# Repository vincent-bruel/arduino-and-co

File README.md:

# arduino-and-co

## Projects involving Arduino, ESP8266, ESP32:
	1. Control a dust collector with magnetic sensors on blast gates

	2. Highlight a photo frame with backlight, led pointing at locations and LCD screen displaying location names

	3. Display weather forecast with an ESP32 and 4x8x8 dot matrix led

	4. Display youtube channel statistics (subscribers) with an ESP32 and 4x8x8 dot matrix led

	5. Get asleep in a few minutes with an arduino Nano and one RGB led like NeoPixel.

   Take a look at my Youtube Channel, there will be Videos for some of these projects.

   I will maintain a list here when they become available:
   
## These projects use my own libraries that are stored in CommonLibraries subdirectory.

## These projects use some third party libraries for which I will maintain a list here.
1. 
2. 
3. 
4. 
5. 
6.

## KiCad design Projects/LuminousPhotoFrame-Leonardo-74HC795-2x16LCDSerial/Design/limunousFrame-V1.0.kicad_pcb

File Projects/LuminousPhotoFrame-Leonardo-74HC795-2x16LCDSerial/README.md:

## Subject: Backlight a photo :camera: (inside a wood or aluminium frame :framed_picture:), 
and place behind some leds and a lcd 16x2 chars
to point/highlight some locations into the photo.

## Example with a polycarbonate front panel

## Schema

## Mandatory Libraries, to install BEFORE programming the sketch to the Arduino:
	Arduino standard SoftwareSerial
	
## Hardware
1. Arduino Leonardo or any Arduino that works with 5V (Nano, Mega, ...)
2. 16 Red led (16 is a maximum)
3. 16 resistor 220ohms 1/4W (16 is a maximum)
4. 2 shift register 74HC795 (each drives 8 leds)
5. Some cable (length depending of your frame's width in centimeters)	
6. A 5V power supply (500mA should be large enough)

## Pinout mapping
See file LuminousFrameFritzing.jpg

## What do you have to tune ?
1. Place leds behind you photo (2cm behind to obtain a sweet spot of approx 1cm on the photo)
2. Change names in the .ino according to the place names or buildings/things you have put a led behind.
3. Put a led strip (NOT controlled by Arduino), around the frame on the back of the photo.

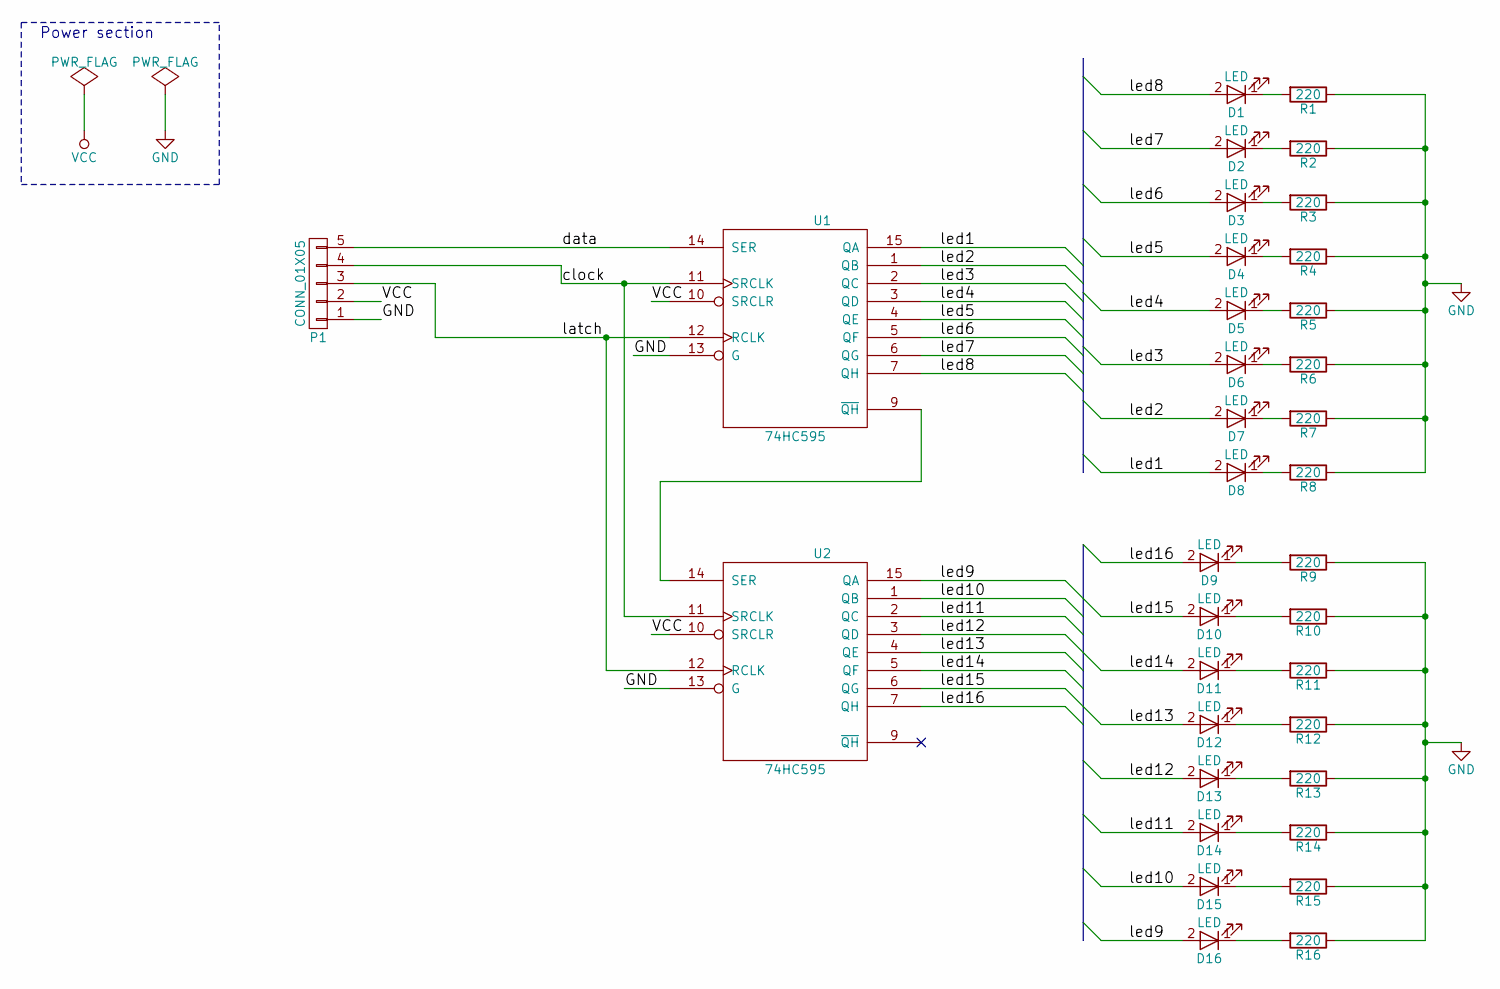
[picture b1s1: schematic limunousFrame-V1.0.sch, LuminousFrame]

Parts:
D1, D2, D3, D4, D5, D6, D7, D8, D9, D10, D11, D12, D13, D14, D15, D16: LED; D_5W_P5.08mm_Vertical_AnodeUp
P1: CONN_01X05; bornier5
R1, R2, R3, R4, R5, R6, R7, R8, R9, R10, R11, R12, R13, R14, R15, R16: 220; R_Axial_Power_L20.0mm_W6.4mm_P5.08mm_Vertical
U1, U2: 74HC595; DIP-16_W7.62mm

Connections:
/clock: P1.4, U1.11 (SRCLK), U2.11 (SRCLK)
/data: P1.5, U1.14 (SER)
/latch: P1.3, U1.12 (RCLK), U2.12 (RCLK)
/led1: D8.2 (A), U1.15 (QA)
/led2: D7.2 (A), U1.1 (QB)
/led3: D6.2 (A), U1.2 (QC)
/led4: D5.2 (A), U1.3 (QD)
/led5: D4.2 (A), U1.4 (QE)
/led6: D3.2 (A), U1.5 (QF)
/led7: D2.2 (A), U1.6 (QG)
/led8: D1.2 (A), U1.7 (QH)
/led9: D16.2 (A), U2.15 (QA)
/led10: D15.2 (A), U2.1 (QB)
/led11: D14.2 (A), U2.2 (QC)
/led12: D13.2 (A), U2.3 (QD)
/led13: D12.2 (A), U2.4 (QE)
/led14: D11.2 (A), U2.5 (QF)
/led15: D10.2 (A), U2.6 (QG)
/led16: D9.2 (A), U2.7 (QH)
GND: P1.1, R1.1, R2.1, R3.1, R4.1, R5.1, R6.1, R7.1, R8.1, R9.1, R10.1, R11.1, R12.1, R13.1, R14.1, R15.1, R16.1, U1.8 (GND), U1.13 (G), U2.8 (GND), U2.13 (G)
unnamed: D1.1 (K), R1.2
unnamed: D2.1 (K), R2.2
unnamed: D3.1 (K), R3.2
unnamed: D4.1 (K), R4.2
unnamed: D5.1 (K), R5.2
unnamed: D6.1 (K), R6.2
unnamed: D7.1 (K), R7.2
unnamed: D8.1 (K), R8.2
unnamed: D9.1 (K), R9.2
unnamed: D10.1 (K), R10.2
unnamed: D11.1 (K), R11.2
unnamed: D12.1 (K), R12.2
unnamed: D13.1 (K), R13.2
unnamed: D14.1 (K), R14.2
unnamed: D15.1 (K), R15.2
unnamed: D16.1 (K), R16.2
unnamed: U1.9 (~QH), U2.14 (SER)
VCC: P1.2, U1.10 (SRCLR), U1.16 (VCC), U2.10 (SRCLR), U2.16 (VCC)

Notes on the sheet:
Power section

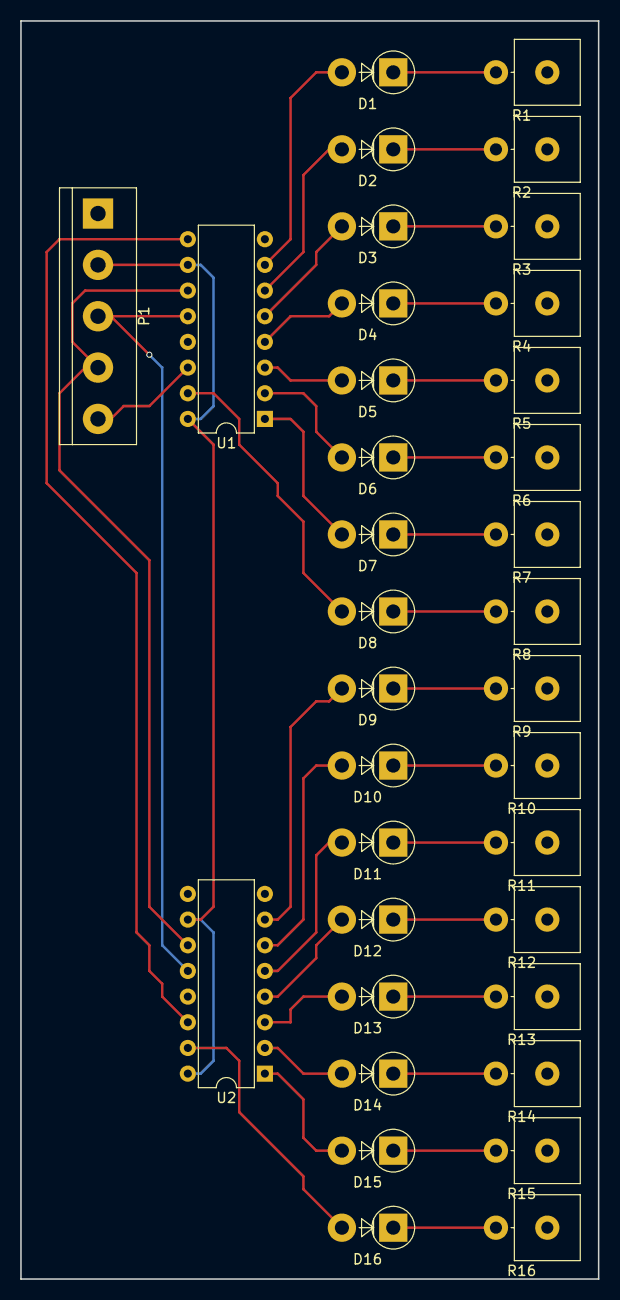
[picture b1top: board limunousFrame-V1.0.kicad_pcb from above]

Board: 2 copper layers, 57.2 x 124.5 mm, 35 parts (0 on the bottom side), 38 nets.

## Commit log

2018-12-25 Modified README
2018-12-25 Add 2 ESP32 projects and 1 common library
2018-12-25 Update lib list
2018-12-25 Add dust collector commander project
2018-12-25 Add new project LuminousPhotoFrame-Leonardo-74HC795-2x16LCDSerial
2018-12-25 Add common hardware ESP32+dotMAtrix
2018-12-25 Point hardware description to CommonHardware
2018-12-25 Fix bug: need to post-pone the Youtube API object creation AFTER EEPROM reading
2018-12-25 Add new project SweetDreams-ArduinoNano-LedWS2813
2018-12-25 Fix readme
2018-12-25 Add library LibEepromDS3231
2018-12-25 Add LibHeaterConsignesInEeprom
2018-12-26 Add design schema
2018-12-26 Add schema link
2018-12-26 Update schema with labels
2018-12-26 Add photo
2018-12-26 Translate procedure
2018-12-26 Add schema for SweetDreams
2018-12-26 Add DustCollectorCommander pinout and schema
2018-12-26 Reorganize project
2018-12-26 Add troubleshooting
2018-12-27 Add HTU21D lib
2018-12-30 Put projects description
2018-12-30 Put links at Mark down format
2018-12-30 Add logical architecture
2018-12-31 Update schema
2018-12-31 Split into multiple sub directories
2018-12-31 Add wiring for motor board
2018-12-31 Add pseudo algorithm for motor board
2019-01-01 Add motor-board sketch
2019-01-03 Add switch board schema
2019-01-04 Describe two architectures: one-line and several-lines
2019-01-05 Add Rotary encoder, 8 digits 7 segments, and 4x A3144 to the schema
2019-01-06 Add note explaining that the Motor-Board is still in development
2019-01-10 Add photos to 3 projects
2019-01-18 Fix bug for displaying delta subscribers correctly
2019-01-18 Unknown modification
2019-01-20 Suppress debug print
2019-01-20 Added video links to Youtube
